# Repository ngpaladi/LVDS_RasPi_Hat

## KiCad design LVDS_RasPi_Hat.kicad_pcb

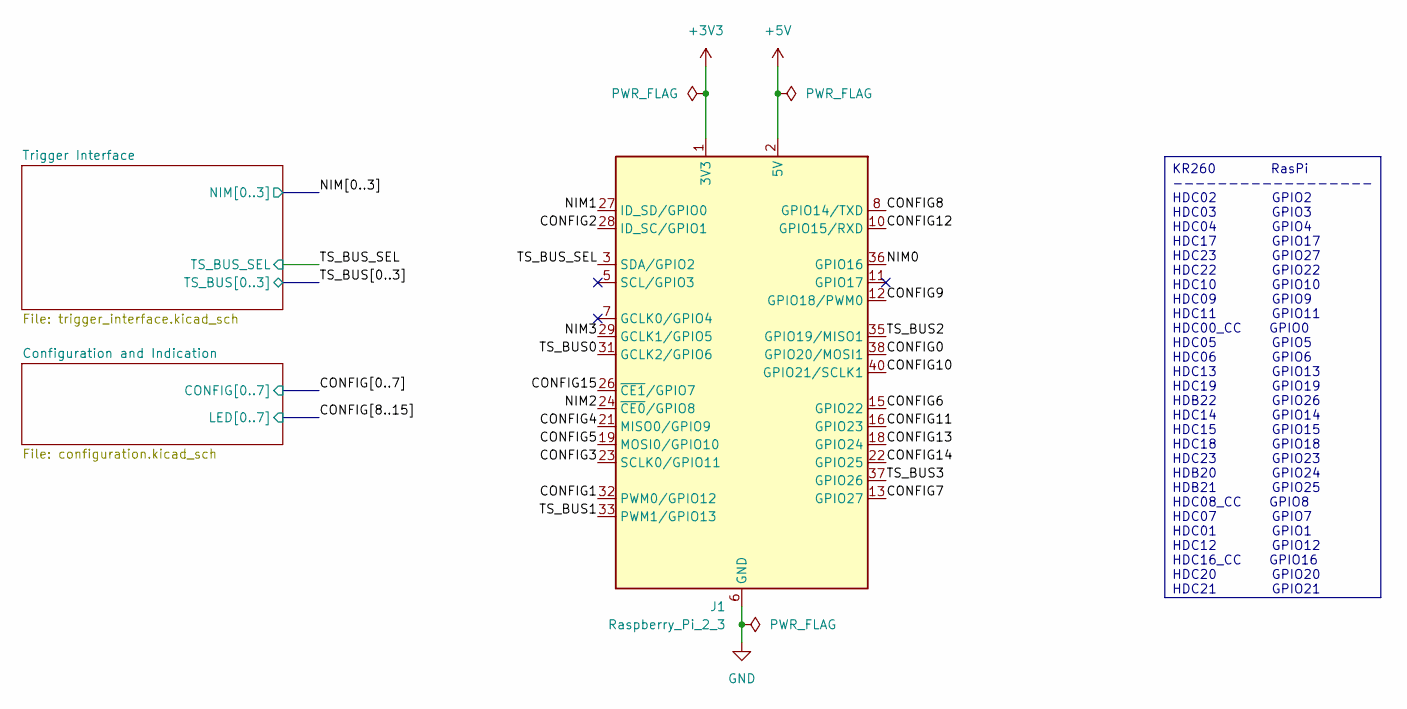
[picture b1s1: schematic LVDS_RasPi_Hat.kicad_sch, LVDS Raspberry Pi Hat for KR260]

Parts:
J1: Raspberry_Pi_2_3; PinSocket_2x20_P2.54mm_Vertical

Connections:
+3V3: J1.1 (3V3), J1.17 (3V3); also elsewhere on the board
+5V: J1.2 (5V), J1.4 (5V)
/CONFIG0: J1.38 (GPIO20/MOSI1); also elsewhere on the board
/CONFIG1: J1.32 (PWM0/GPIO12); also elsewhere on the board
/CONFIG2: J1.28 (ID_SC/GPIO1); also elsewhere on the board
/CONFIG3: J1.23 (SCLK0/GPIO11); also elsewhere on the board
/CONFIG4: J1.21 (MISO0/GPIO9); also elsewhere on the board
/CONFIG5: J1.19 (MOSI0/GPIO10); also elsewhere on the board
/CONFIG6: J1.15 (GPIO22); also elsewhere on the board
/CONFIG7: J1.13 (GPIO27); also elsewhere on the board
/CONFIG8: J1.8 (GPIO14/TXD); also elsewhere on the board
/CONFIG9: J1.12 (GPIO18/PWM0); also elsewhere on the board
/CONFIG10: J1.40 (GPIO21/SCLK1); also elsewhere on the board
/CONFIG11: J1.16 (GPIO23); also elsewhere on the board
/CONFIG12: J1.10 (GPIO15/RXD); also elsewhere on the board
/CONFIG13: J1.18 (GPIO24); also elsewhere on the board
/CONFIG14: J1.22 (GPIO25); also elsewhere on the board
/CONFIG15: J1.26 (~CE1/GPIO7); also elsewhere on the board
/NIM0: J1.36 (GPIO16); also elsewhere on the board
/NIM1: J1.27 (ID_SD/GPIO0); also elsewhere on the board
/NIM2: J1.24 (~CE0/GPIO8); also elsewhere on the board
/NIM3: J1.29 (GCLK1/GPIO5); also elsewhere on the board
/TS_BUS0: J1.31 (GCLK2/GPIO6); also elsewhere on the board
/TS_BUS1: J1.33 (PWM1/GPIO13); also elsewhere on the board
/TS_BUS2: J1.35 (GPIO19/MISO1); also elsewhere on the board
/TS_BUS3: J1.37 (GPIO26); also elsewhere on the board
/TS_BUS_SEL: J1.3 (SDA/GPIO2); also elsewhere on the board
GND: J1.6 (GND), J1.9 (GND), J1.14 (GND), J1.20 (GND), J1.25 (GND), J1.30 (GND), J1.34 (GND), J1.39 (GND); also elsewhere on the board

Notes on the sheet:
KR260 RasPi ------------------ HDC02 GPIO2 HDC03 GPIO3 HDC04 GPIO4 HDC17 GPIO17 HDC23 GPIO27 HDC22 GPIO22 HDC10 GPIO10 HDC09 GPIO9 HDC11 GPIO11 HDC00_CC GPIO0 HDC05 GPIO5 HDC06 GPIO6 HDC13 GPIO13 HDC19 GPIO19 HDB22 GPIO26 HDC14 GPIO14 HDC15 GPIO15 HDC18 GPIO18 HDC23 GPIO23 HDB20 GPIO24 HDB21 GPIO25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

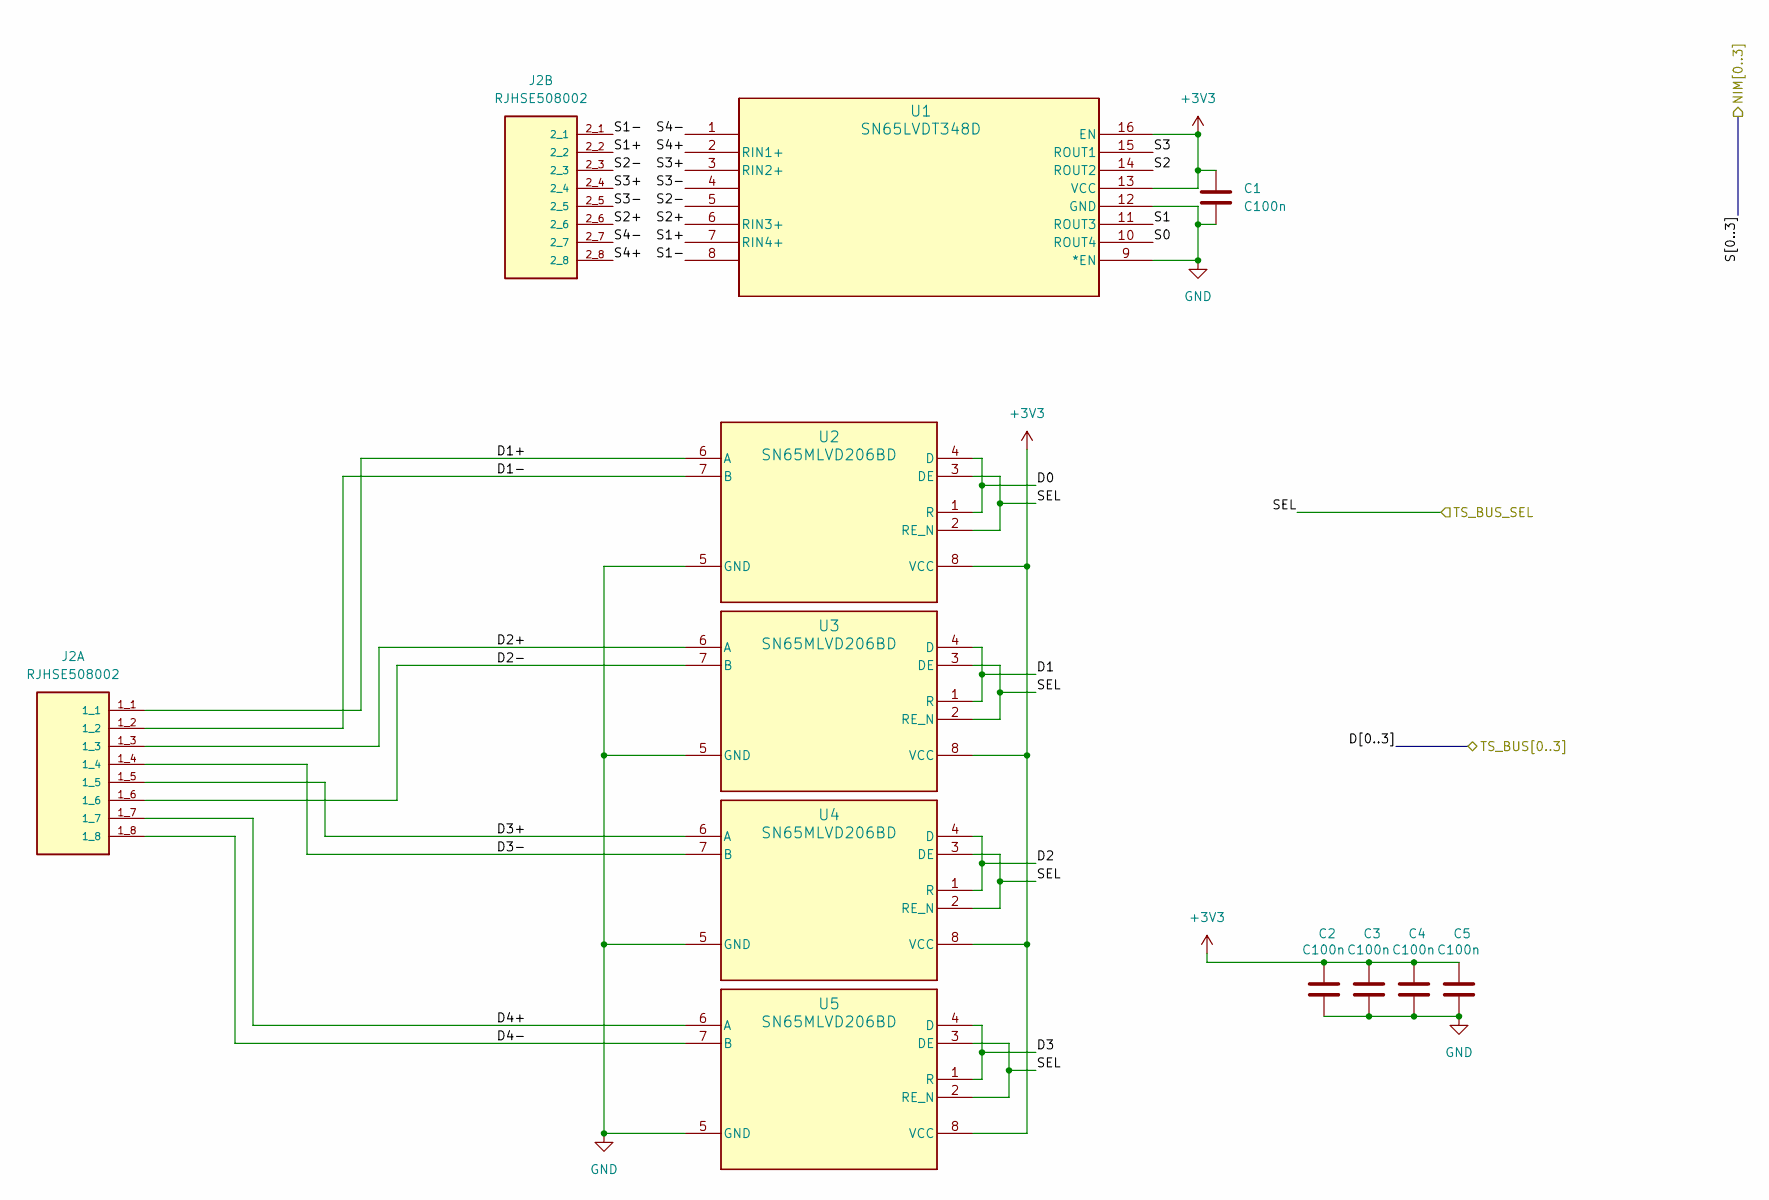
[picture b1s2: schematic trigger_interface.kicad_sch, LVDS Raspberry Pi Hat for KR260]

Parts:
C1, C2, C3, C4, C5: C100n; C_0402_1005Metric_Pad0.74x0.62mm_HandSolder
J2: RJHSE508002; AMPHENOL_RJHSE508002; PARTREV E
U1: SN65LVDT348D; D16
U2, U3, U4, U5: SN65MLVD206BD; D0008A_N

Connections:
+3V3: C1.1, C2.1, C3.1, C4.1, C5.1, U1.13 (VCC), U1.16 (EN), U2.8 (VCC), U3.8 (VCC), U4.8 (VCC), U5.8 (VCC); also elsewhere on the board
/NIM0: U1.10 (ROUT4); also elsewhere on the board
/NIM1: U1.11 (ROUT3); also elsewhere on the board
/NIM2: U1.14 (ROUT2); also elsewhere on the board
/NIM3: U1.15 (ROUT1); also elsewhere on the board
/TS_BUS0: U2.1 (R), U2.4 (D); also elsewhere on the board
/TS_BUS1: U3.1 (R), U3.4 (D); also elsewhere on the board
/TS_BUS2: U4.1 (R), U4.4 (D); also elsewhere on the board
/TS_BUS3: U5.1 (R), U5.4 (D); also elsewhere on the board
/TS_BUS_SEL: U2.2 (RE_N), U2.3 (DE), U3.2 (RE_N), U3.3 (DE), U4.2 (RE_N), U4.3 (DE), U5.2 (RE_N), U5.3 (DE); also elsewhere on the board
/Trigger Interface/D1+: J2.1_1, U2.6 (A)
/Trigger Interface/D1-: J2.1_2, U2.7 (B)
/Trigger Interface/D2+: J2.1_3, U3.6 (A)
/Trigger Interface/D2-: J2.1_6, U3.7 (B)
/Trigger Interface/D3+: J2.1_5, U4.6 (A)
/Trigger Interface/D3-: J2.1_4, U4.7 (B)
/Trigger Interface/D4+: J2.1_7, U5.6 (A)
/Trigger Interface/D4-: J2.1_8, U5.7 (B)
/Trigger Interface/S1+: J2.2_2, U1.7 (RIN4+)
/Trigger Interface/S1-: J2.2_1, U1.8
/Trigger Interface/S2+: J2.2_6, U1.6 (RIN3+)
/Trigger Interface/S2-: J2.2_3, U1.5
/Trigger Interface/S3+: J2.2_4, U1.3 (RIN2+)
/Trigger Interface/S3-: J2.2_5, U1.4
/Trigger Interface/S4+: J2.2_8, U1.2 (RIN1+)
/Trigger Interface/S4-: J2.2_7, U1.1
GND: C1.2, C2.2, C3.2, C4.2, C5.2, U1.9 (*EN), U1.12 (GND), U2.5 (GND), U3.5 (GND), U4.5 (GND), U5.5 (GND); also elsewhere on the board

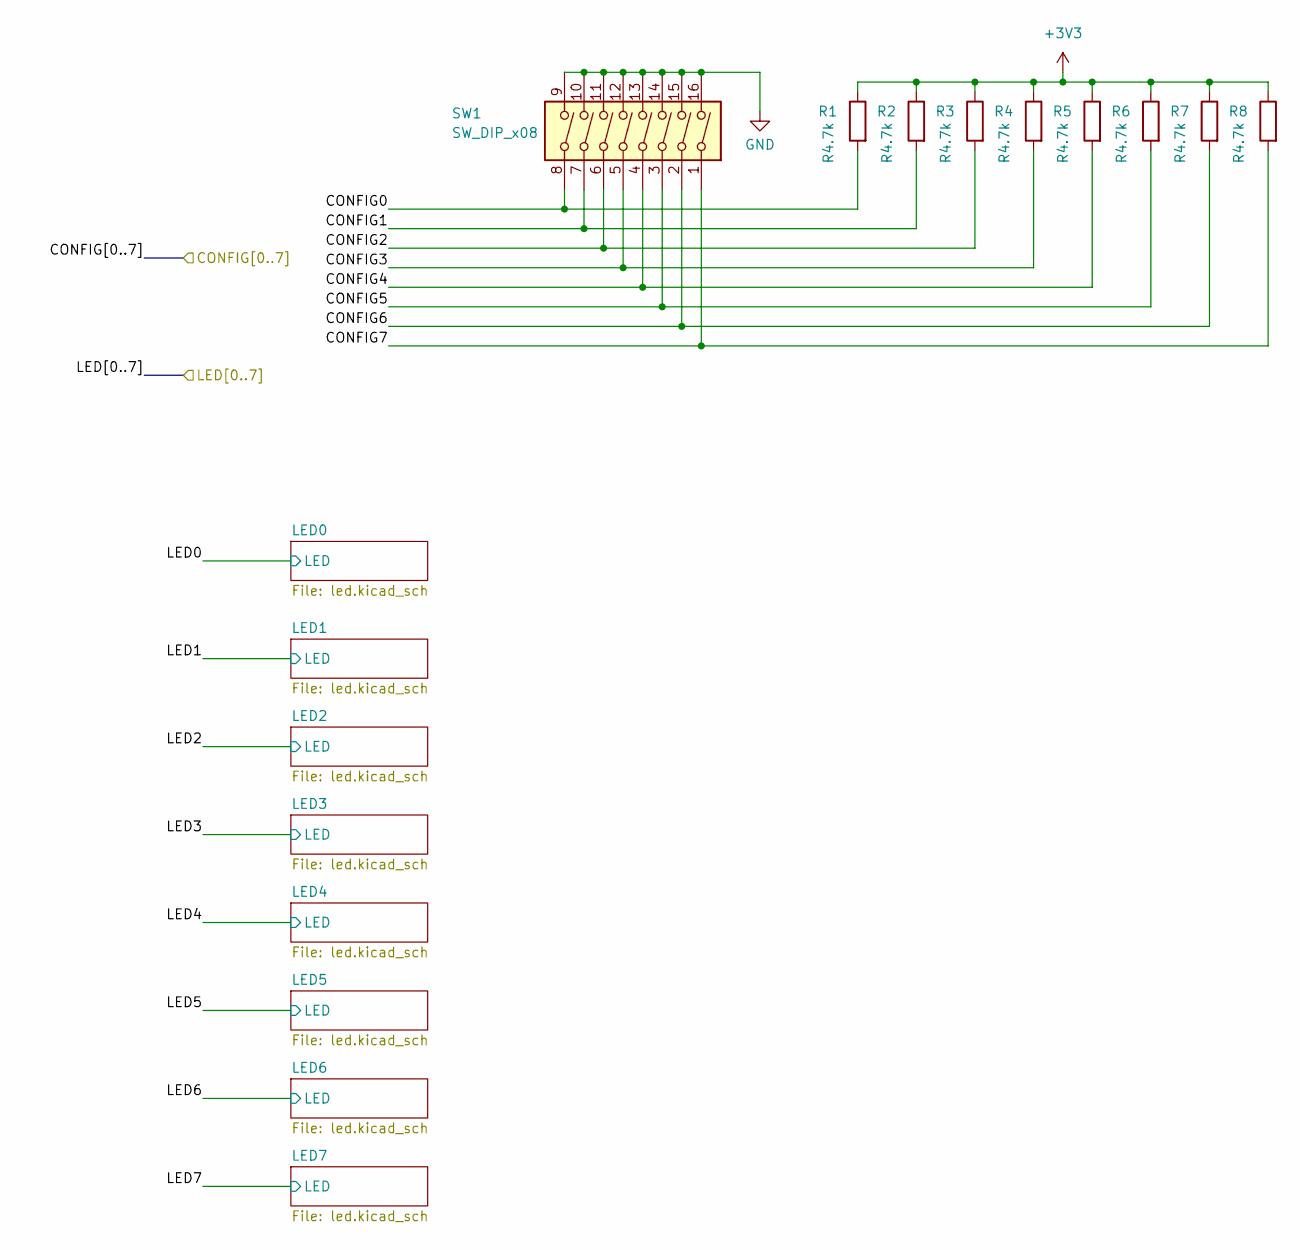
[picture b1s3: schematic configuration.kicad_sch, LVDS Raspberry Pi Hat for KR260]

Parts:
R1, R2, R3, R4, R5, R6, R7, R8: R4.7k; R_0402_1005Metric_Pad0.72x0.64mm_HandSolder
SW1: SW_DIP_x08; 219-8LPST_CTS-M

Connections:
+3V3: R1.1, R2.1, R3.1, R4.1, R5.1, R6.1, R7.1, R8.1; also elsewhere on the board
/CONFIG0: R1.2, SW1.8; also elsewhere on the board
/CONFIG1: R2.2, SW1.7; also elsewhere on the board
/CONFIG2: R3.2, SW1.6; also elsewhere on the board
/CONFIG3: R4.2, SW1.5; also elsewhere on the board
/CONFIG4: R5.2, SW1.4; also elsewhere on the board
/CONFIG5: R6.2, SW1.3; also elsewhere on the board
/CONFIG6: R7.2, SW1.2; also elsewhere on the board
/CONFIG7: R8.2, SW1.1; also elsewhere on the board
GND: SW1.9, SW1.10, SW1.11, SW1.12, SW1.13, SW1.14, SW1.15, SW1.16; also elsewhere on the board

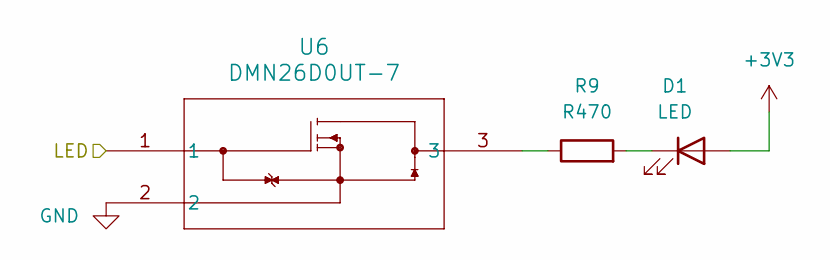
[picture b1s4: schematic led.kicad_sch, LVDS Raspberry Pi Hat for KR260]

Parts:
D1: LED; LED_0402_1005Metric_Pad0.77x0.64mm_HandSolder
R9: R470; R_0402_1005Metric_Pad0.72x0.64mm_HandSolder
U6: DMN26D0UT-7; DMN26D0UT-7_PER

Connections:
+3V3: D1.2 (A); also elsewhere on the board
/CONFIG8: U6.1; also elsewhere on the board
GND: U6.2; also elsewhere on the board
unnamed: D1.1 (K), R9.2
unnamed: R9.1, U6.3

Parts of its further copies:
D2, D3, D4, D5, D6, D7, D8: LED; LED_0402_1005Metric_Pad0.77x0.64mm_HandSolder
R10, R11, R12, R13, R14, R15, R16: R470; R_0402_1005Metric_Pad0.72x0.64mm_HandSolder
U7, U8, U9, U10, U11, U12, U13: DMN26D0UT-7; DMN26D0UT-7_PER

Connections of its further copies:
+3V3: D2.2 (A), D3.2 (A), D4.2 (A), D5.2 (A), D6.2 (A), D7.2 (A), D8.2 (A); also elsewhere on the board
/CONFIG9: U7.1; also elsewhere on the board
/CONFIG10: U8.1; also elsewhere on the board
/CONFIG11: U9.1; also elsewhere on the board
/CONFIG12: U10.1; also elsewhere on the board
/CONFIG13: U11.1; also elsewhere on the board
/CONFIG14: U12.1; also elsewhere on the board
/CONFIG15: U13.1; also elsewhere on the board
GND: U7.2, U8.2, U9.2, U10.2, U11.2, U12.2, U13.2; also elsewhere on the board
unnamed: D2.1 (K), R10.2
unnamed: D3.1 (K), R11.2
unnamed: D4.1 (K), R12.2
unnamed: D5.1 (K), R13.2
unnamed: D6.1 (K), R14.2
unnamed: D7.1 (K), R15.2
unnamed: D8.1 (K), R16.2
unnamed: R10.1, U7.3
unnamed: R11.1, U8.3
unnamed: R12.1, U9.3
unnamed: R13.1, U10.3
unnamed: R14.1, U11.3
unnamed: R15.1, U12.3
unnamed: R16.1, U13.3

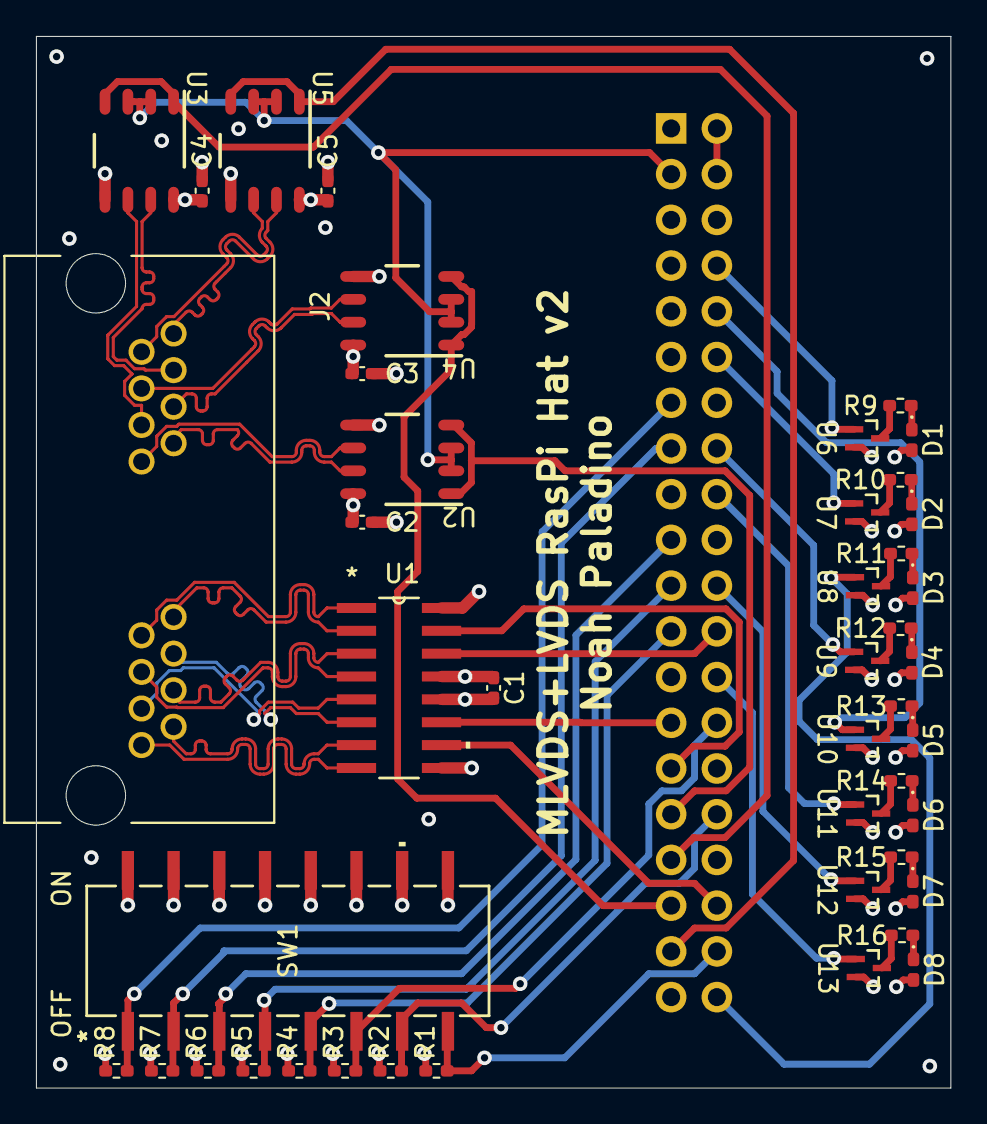
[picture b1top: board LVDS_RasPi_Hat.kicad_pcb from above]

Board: 4 copper layers, 50.8 x 58.4 mm, 45 parts (1 on the bottom side), 60 nets.
